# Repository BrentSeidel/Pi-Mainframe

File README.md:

# Pi-Mainframe
Simulated mainframe computer based on a Raspberry Pi

[]
(https://alire.ada.dev/crates/blinkenlights.html)

When I was a young lad, computers had complicated panels filled with
switches and lights.  Sadly, these disappeared as I got older.

This project is an attempt to recreate the feel of old mainframe computers
using a Raspberry Pi 3 and some other assorted parts that I had laying
around.  The actual boxes and panels are 3D printed.

Here is an example system.  Note that it is fairly modular and the
modules can be attached in different ways.

Back of system

## Note
This is still very much a work in progress and things will change.

This project requires 3D printing, making PCBs, soldering, and building
software from source.  It might be a good project for an undergraduate
engineering program.

## Power
I originally used a random micro USB power supply for the Pi 3 that is
running the simulation.  It would complain about low voltage and
occasionally reboot.  I just replaced it with the official Raspberry Pi
power supply and it is not complaining about low voltage.  Time will
tell if it is more stable.

Ultimately, there will be limits to how much power you can get out of
the Raspberry Pi.  There are ways to reduce the power needed.  The first
thing that I would try would be to increase the value of the resistors
for the LEDs.  This would also reduce the brightness so you may wish to
do this as well, if the LEDs are too bright.  A little experimentation
will be needed to determine the proper value.  From a BOM viewpoint,
using the same resistors for both the switches and LEDs would be a win.

## PCBs
Three printed circuit boards have been designed to eliminate some of the
tedious soldering.  Using the PCBs make assembly much easier and the
resulting project much less of a mess of wires.

### IO Board PCB
The I/O board PCB has been created and tested.  The schematics and PCB
layout have been moved to the Circuits reporitory.  Documentation and
assembly instructions for it have been created there.

### Breakout PCB
A breakout PCB has been developed for breaking out the 10 conductor
ribbon cables that are being used for the I2C bus, and other uses.  It
is also in the Circuits repository.

### LED PCB
A PCB has been developed for holding the LEDs.  This required some redesign
to the panels.  However it eliminates the soldering of wires directly to
the LED leads.  The LED PCB can also be fairly easily added to and
removed from panels should you wish to, for example, use LEDs of different
colors.

## Dependencies
This depends on the following repositories:
* https://github.com/BrentSeidel/BBS-Ada.git
* https://github.com/BrentSeidel/BBS-BBB-Ada.git
* https://github.com/BrentSeidel/Ada-Web-Server.git
* https://github.com/BrentSeidel/Things.git
* https://github.com/BrentSeidel/Sim-CPU.git
* https://github.com/BrentSeidel/Circuits.git

If you are actually interested in simulating old computers, you can
download and build simh from github at https://github.com/simh/simh.git
I was able to get the PDP-11 sim to build (I haven't tried others) and
run on a Raspberry Pi.  As far as I know, it has no support for blinking
lights.

You could, of course run simh in parallel with this project giving a
CPU simulation as well as lights and switches.  Unfortunately, they would
be completely independant.  Someday, perhaps this will change.

## Assembly
This project will require quite a bit of 3D printing and soldering.  The
included documentation includes a parts list.  Read the documentation
first, then download the dependencies repositories.  Finally decided
how big of a system you want.
1. Slice the 3D models and start them printing.  This will take a while,
   so start this first and then work on other things while they are printing.
2. Install Raspberian on the Raspberry Pi and install the following packages:
   * avahi - This allows discovery on your local network
   * gnat - The GNU Ada distribution
   * gprbuild - Used for building Ada software
3. Build the software.  If there are errors about missing "obj" directories,
   create the directories.
4. Start soldering the various boards and cables.
5. As panels come off the printer, install LEDs and switches as appropriate
6. As the trays come off the printer, install the boards and connectors.
7. Once everything is printed, put all the pieces together.

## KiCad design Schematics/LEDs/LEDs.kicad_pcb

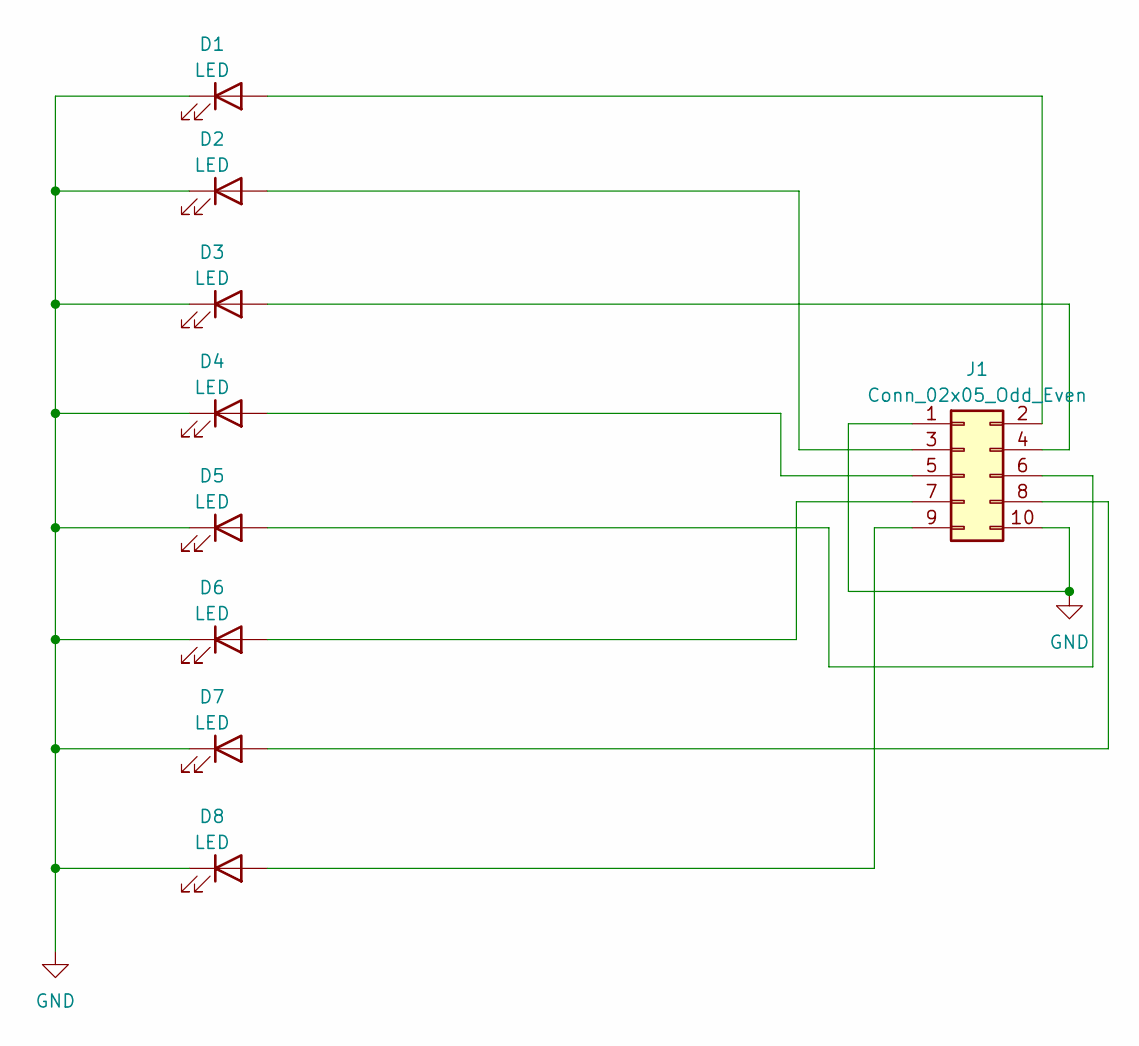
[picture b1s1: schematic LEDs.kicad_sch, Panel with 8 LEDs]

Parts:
D1, D2, D3, D4, D5, D6, D7, D8: LED; LED_D5.0mm_Clear
J1: Conn_02x05_Odd_Even; PinHeader_2x05_P2.54mm_Horizontal

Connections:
GND: D1.1 (K), D2.1 (K), D3.1 (K), D4.1 (K), D5.1 (K), D6.1 (K), D7.1 (K), D8.1 (K), J1.1, J1.10
unnamed: D1.2 (A), J1.2
unnamed: D2.2 (A), J1.3
unnamed: D3.2 (A), J1.4
unnamed: D4.2 (A), J1.5
unnamed: D5.2 (A), J1.6
unnamed: D6.2 (A), J1.7
unnamed: D7.2 (A), J1.8
unnamed: D8.2 (A), J1.9

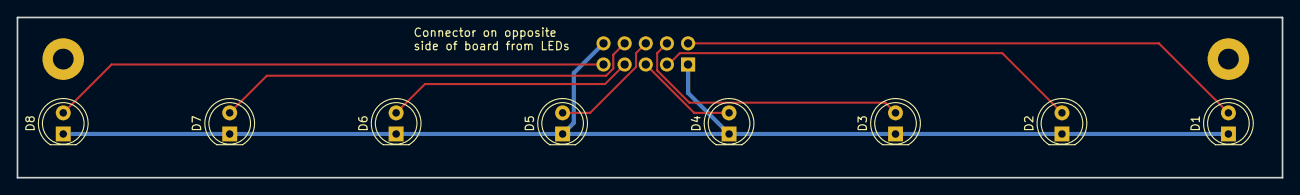
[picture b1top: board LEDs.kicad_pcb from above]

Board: 2 copper layers, 152.0 x 19.2 mm, 11 parts (1 on the bottom side), 9 nets.

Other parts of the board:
REF1, REF2: MountingHole_2.5mm_Pad

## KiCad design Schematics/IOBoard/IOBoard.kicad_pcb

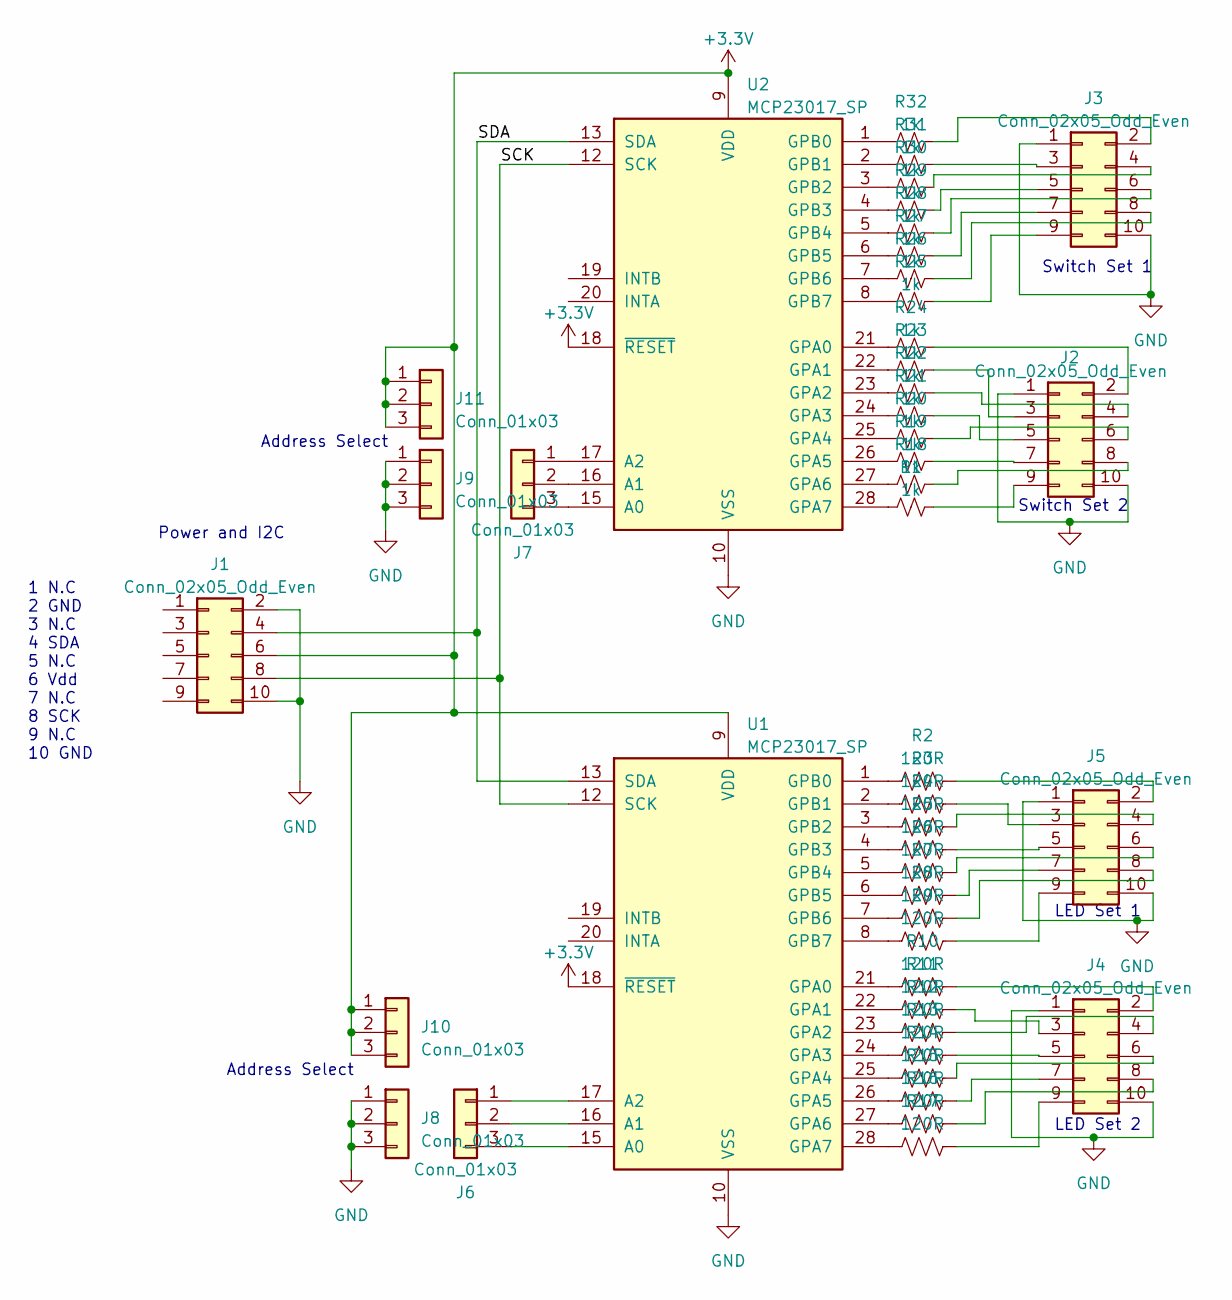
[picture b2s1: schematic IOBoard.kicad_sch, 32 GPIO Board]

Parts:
J1, J2, J3, J4, J5: Conn_02x05_Odd_Even; PinHeader_2x05_P2.54mm_Horizontal
J6, J7, J8, J9, J10, J11: Conn_01x03; PinSocket_1x03_P2.54mm_Vertical
R1, R18, R19, R20, R21, R22, R23, R24, R25, R26, R27, R28, R29, R30, R31, R32: 1k; R_1206_3216Metric_Pad1.30x1.75mm_HandSolder
R2, R3, R4, R5, R6, R7, R8, R9, R10, R11, R12, R13, R14, R15, R16, R17: 120R; R_1206_3216Metric_Pad1.30x1.75mm_HandSolder
U1, U2: MCP23017_SP; DIP-28_W7.62mm

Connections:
+3.3V: J1.6, J10.1, J10.2, J10.3, J11.1, J11.2, J11.3, U1.9 (VDD), U1.18 (~RESET), U2.9 (VDD), U2.18 (~RESET)
/SCK: J1.8, U1.12 (SCK), U2.12 (SCK)
/SDA: J1.4, U1.13 (SDA), U2.13 (SDA)
GND: J1.2, J1.10, J2.1, J2.10, J3.1, J3.10, J4.1, J4.10, J5.1, J5.10, J8.1, J8.2, J8.3, J9.1, J9.2, J9.3, U1.10 (VSS), U2.10 (VSS)
unnamed: J2.2, R24.2
unnamed: J2.3, R23.2
unnamed: J2.4, R22.2
unnamed: J2.5, R21.2
unnamed: J2.6, R20.2
unnamed: J2.7, R19.2
unnamed: J2.8, R18.2
unnamed: J2.9, R1.2
unnamed: J3.2, R32.2
unnamed: J3.3, R31.2
unnamed: J3.4, R30.2
unnamed: J3.5, R29.2
unnamed: J3.6, R28.2
unnamed: J3.7, R27.2
unnamed: J3.8, R26.2
unnamed: J3.9, R25.2
unnamed: J4.2, R10.1
unnamed: J4.3, R11.1
unnamed: J4.4, R12.1
unnamed: J4.5, R13.1
unnamed: J4.6, R14.1
unnamed: J4.7, R15.1
unnamed: J4.8, R16.1
unnamed: J4.9, R17.1
unnamed: J5.2, R2.1
unnamed: J5.3, R3.1
unnamed: J5.4, R4.1
unnamed: J5.5, R5.1
unnamed: J5.6, R6.1
unnamed: J5.7, R7.1
unnamed: J5.8, R8.1
unnamed: J5.9, R9.1
unnamed: J6.1, U1.17 (A2)
unnamed: J6.2, U1.16 (A1)
unnamed: J6.3, U1.15 (A0)
unnamed: J7.1, U2.17 (A2)
unnamed: J7.2, U2.16 (A1)
unnamed: J7.3, U2.15 (A0)
unnamed: R10.2, U1.21 (GPA0)
unnamed: R11.2, U1.22 (GPA1)
unnamed: R12.2, U1.23 (GPA2)
unnamed: R13.2, U1.24 (GPA3)
unnamed: R14.2, U1.25 (GPA4)
unnamed: R15.2, U1.26 (GPA5)
unnamed: R16.2, U1.27 (GPA6)
unnamed: R17.2, U1.28 (GPA7)
unnamed: R2.2, U1.1 (GPB0)
unnamed: R3.2, U1.2 (GPB1)
unnamed: R4.2, U1.3 (GPB2)
unnamed: R5.2, U1.4 (GPB3)
unnamed: R6.2, U1.5 (GPB4)
unnamed: R7.2, U1.6 (GPB5)
unnamed: R8.2, U1.7 (GPB6)
unnamed: R9.2, U1.8 (GPB7)
unnamed: R24.1, U2.21 (GPA0)
unnamed: R23.1, U2.22 (GPA1)
unnamed: R22.1, U2.23 (GPA2)
unnamed: R21.1, U2.24 (GPA3)
unnamed: R20.1, U2.25 (GPA4)
unnamed: R19.1, U2.26 (GPA5)
unnamed: R18.1, U2.27 (GPA6)
unnamed: R1.1, U2.28 (GPA7)
unnamed: R32.1, U2.1 (GPB0)
unnamed: R31.1, U2.2 (GPB1)
unnamed: R30.1, U2.3 (GPB2)
unnamed: R29.1, U2.4 (GPB3)
unnamed: R28.1, U2.5 (GPB4)
unnamed: R27.1, U2.6 (GPB5)
unnamed: R26.1, U2.7 (GPB6)
unnamed: R25.1, U2.8 (GPB7)

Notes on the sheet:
1 N.C 2 GND 3 N.C 4 SDA 5 N.C 6 Vdd 7 N.C 8 SCK 9 N.C 10 GND
Power and I2C
Switch Set 1
Address Select
LED Set 1
LED Set 2
Switch Set 2

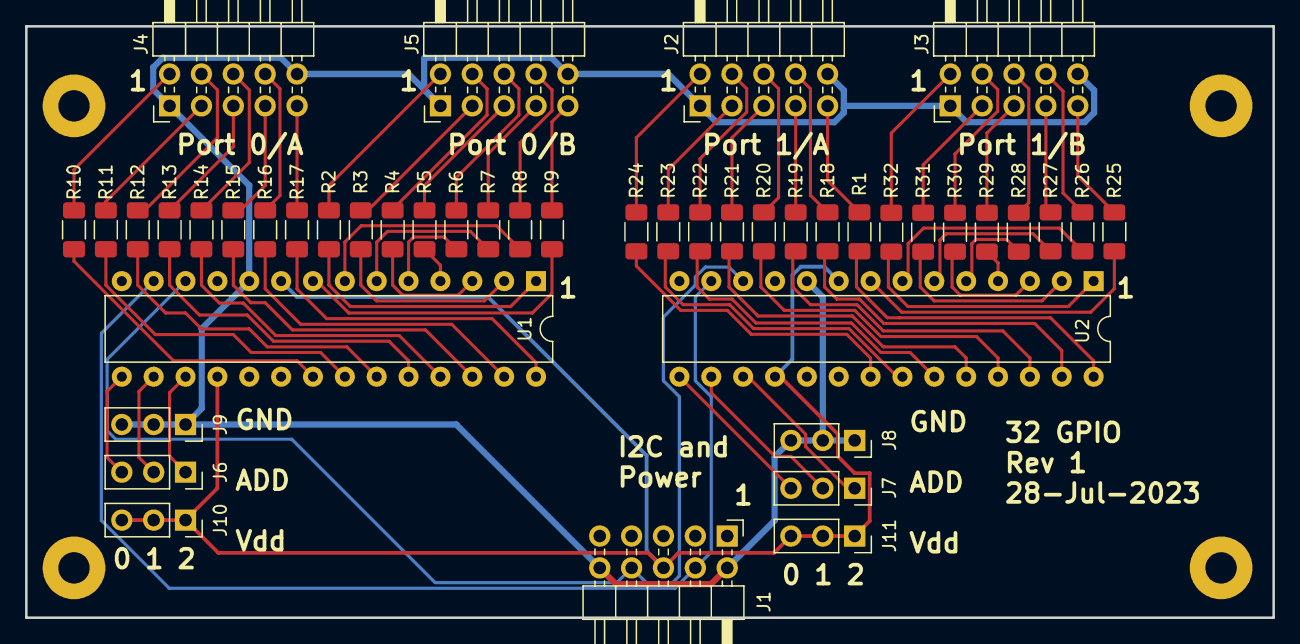
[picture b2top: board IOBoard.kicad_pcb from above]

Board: 2 copper layers, 99.4 x 47.1 mm, 49 parts (0 on the bottom side), 74 nets.

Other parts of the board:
H1, H2, H3, H4: MountingHole_2.5mm_Pad

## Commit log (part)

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2021-09-12 First commit with OpenSCAD files for 3D printed objects.
2021-09-12 Add the initial Ada software.
2021-09-14 Use enumeration with representation clauses for MCP23017 devices so that the addresses are encapsulated.
    Update project file to reference Ada-Web-Server.
2021-09-14 Typo correction - change i2c.SWITCH_MSW to i2c.SWITCH_LSW.
2021-09-15 Add web server - it doesn't do much yet. Change patterns to a task.
2021-09-15 Restructure the patterns code to eliminate a circular dependency.
2021-09-15 Further web server development - add a page to show hardware configuration.
2021-09-16 Add documentation files with outlines.
2021-09-17 Start working on documentation and add documentation to web pages.
2021-09-21 Restructure code a bit and start adding AJAX for interfacing to the simulator via a web page.
2021-09-21 Updates to start to allow remote control of simulator.
2021-09-22 Some doc and hardware updates. Work on interface between i2c and simulator.
2021-09-22 Work on simulator interface some more.
2021-09-23 Add display of panel register values.
2021-09-23 Documentation updates and a minor update to control panel labels.
2021-09-28 Documentation updates and add some assembly pictures.
2021-09-29 Documentation updates with figures to add instructions for wiring LEDs on panels.
2021-10-05 Documentation updates. Add a power panel. S/W updates to start working witn control and mode panels.
2021-10-06 Documentation updates and add a couple of assembly images.
2021-10-07 More documentation updates.
2021-10-08 Documentation updates - add more assembly instructions and photos.
2021-10-08 Update hardware configuration code to support mode/control LEDs.
2021-10-08 Extend test patterns to include mode/control LEDs.
2021-10-08 Minor tweaks to test patterns.
2021-10-08 Minor tweaks to test patterns. Add a construction photo for later inclusion into documentation.
2021-10-10 Update software to be able to test control switches.
2021-10-11 Initial code to let the auto/man switch enable/disable remote control.
2021-10-12 Update documentation to show switch wiring.
    Increase size of rack flanges and work on incorporating control switch
    functions into software.
    Process pictures to reduce their size and the size of the documents.
    Squashed some commits to avoid sending too large files to GitHub.
2021-10-12 Fix bug in allowing deposit to select test pattern.
2021-10-12 Move exception handler to top level to turn out the lights when exiting. Some changes to switch change logic to clear changes at the end of the loop.
2021-10-13 More work on control switch logic and reduction of redundant I2C messages.
2021-10-13 Allow web server to request simulator exit
2021-10-15 Documentation updates and some minor internal changes to simulator. Adjust the spacing of mounting holes for rack adapters.
2021-10-20 Add program to test lights and switches
2021-10-20 Updates to lamp test.
2021-10-21 Add 16 and 32 bit versions of bounce and scan test patterns.
2021-10-21 Update web page javascript to account for new sim patterns.
2021-10-22 Documentation updates.
2021-11-22 Correct typo in documentation.
2022-01-10 Start work on using represenation clauses for boolean values rather than doing the bit twiddling in code.
2022-01-10 More work on using representation clauses.
2022-01-10 More cleanup from represenation clauses.
2022-01-11 More cleanup with represenation clauses.
2022-01-11 Make switch register values read-only outside of sim package.
2022-01-11 Rename package "sim" to "panel" in preparation for separating the panel interface from the simulators.
2022-01-11 More cleanup and refactoring.
2022-01-12 Fix bug related to detecting switch changes.
2022-01-13 Start work on breaking simulators out from panels.
2022-01-13 More work on turning simulator into an object.
2022-01-13 Start removing old simulator code from panels package.
2022-01-14 Updates to simulator interface.
2022-01-14 Fill in code for deposit to show the value deposited.
2022-01-18 Change way that Address/Data switch is handled. Start preparing simulator for breakout into a separate repository.
2022-01-18 Move simulators into BBS package hierarchy. Add web page to show simulator information and register values.
2022-01-18 Fix stub return register value routine to actually return register value instead of 0.
2022-01-19 Updates to improve the display of register values.
2022-01-19 Move definitions for mode/control types to sim package.
2022-01-19 Remove simulator dependence on Panel package.
2022-01-19 Add missing code to communicate panel data with the simulator.
2022-01-20 Some internal code cleanup and make the simulator control web page ensure that the correct simulator is running.
2022-01-21 Change package name "Sim" to "Sim_CPU" as I may wish to support other kinds of simulations. Other minor code cleanup.
2022-01-21 Moved simulator files into Sim-CPU repository and made updates to point to that project. Also fixed a couple typos in comments in i2c.ads
2022-01-21 Update README to point to Sim-CPU repository as a dependency.
2023-05-28 Start working on schematics and board layout for I/O board. If nothing else, the schematics will provide some documentation about how things should be wired up. Note that this may not be consistent w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
2023-06-13 Update schematic and PCB to use resistor symbols instead of jumpers.
2023-06-19 Update PCB to use SMD resistors and rectangular connectors. This lets the PCB shrink some more and it may be easier to crimp rectangular connectors onto ribbon cable than to solder a bunch of D-9 con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
2023-07-09 Update schematic to add resisters on inputs as well. Submitted PCB for production. Once PCBs are received, assembled, tested, and working, I'll update documentation.
2023-07-24 Fix schematic error and re-layout board. Start a tray to hold board.
2023-07-26 More updates to I/O board PCB layout.
2023-07-28 Updates to PCB layout to add silkscreen blocks for notes.
2023-08-09 Updates to panels. Delete unused stuff and modify labels.
2023-08-11 Remove I/O Board design now that it has been moved to the Circuits repository.
2023-08-14 Update README.md
    Correct typo in link to Circuits repository.
2023-08-15 Work on CPU tray to incorporate the breakout board from the circuits repository. Work on I/O tray to use the new GPIO board from the circuits repository.
2023-08-15 Use Ribbon-10 breakout board model instead of local breakout model.
2023-08-17 Add PCB for LEDs and update panels to use the PCB.
2023-08-18 Update the README to give current status.
2023-08-30 Adjust the IO tray so that the IO board lines up with the connector from the processor board. This makes the ribbon cable easier to run.
2023-08-31 Move documentation to prepare for documentation for new hardware. Also minor change to code to be consistent with changes to Sim-CPU.
2023-09-01 Start working on assmebly instructions for new hardware with custom PCBs.
2023-09-01 Update panels for LED PCBs.
2023-09-04 Add documentation for assembling the LED PCBs.
2023-09-04 Updates to lamp test program to add a sequence pattern.
2023-09-04 Updates to documentation to include assembly of panels.
2023-09-05 More documentation updates. The new documentation should be nearly complete.
2023-09-05 Minor updates to documentation primarily to fix table references.
2023-09-06 Remove some old hardware details from new hardware documentation.
2023-09-06 Minor updates to start working with multiple simulations.
2023-09-13 Add photos of a completed system.
2023-09-13 Update README.md
    Fix markdown code for image in README.
2023-09-19 Update to README about power supply and consumption/
2023-09-20 Minor changes to support hardware debugging and cleanup.
2023-11-06 Correct spelling of "engergisze" on power panel, per Issue #1.
2023-11-06 Update README.md
    Delete extra backslash from LED PCB heading.
2023-11-14 Updates to run with 8080 simulator.
2023-11-15 Updates to improve status LED display.
2024-01-22 Updates to be consistent with changes in other projets (mainly uint definitions moving from BBS.embed to BBS.
2024-03-20 Updates to add 68000 simulator and make work with other package changes.
2024-03-20 Call initialization for 68000 CPU. Add sample OS and Task files for 68000 CPU. Move project to use alire.
2024-05-02 Update code to allow simulator selection on program entry.
2024-05-07 Add missing attach of clock to 68000 init. Add mux device to 68000 init.
2024-05-07 Add line to set the clock's base rate. Add updated OS68k.
2024-05-07 Add updated tasks for OS68k.
2024-08-07 Updates to account for changes in other projects.
2024-08-09 Update *.gpr files to account for changes to BBS-BBB-Ada (bbs.embed.* packages).
2024-08-14 Rename projects and executables in preparation for alr publish.
2024-08-14 Prepare for alr publish.
2024-08-14 Update version number.
2024-08-20 Add alire badge to README.
2024-09-11 Update to work with MCP23017 changes. Update to new alire version number. Fix *_noalire.gpr project name.
2024-09-20 Use I2C addresses from BBS.embed.i2c.devices.
2025-03-09 Update to work with the latest (v0.3.2) version of bbs_simcpu.
2025-03-10 Change dependency in bbs_embed_linux to 0.2.0
2025-03-10 Fix alr dependencies.
2025-03-10 Update alr dependency on bbs-embed-linux to v0.2.0.
2025-09-16 Updates to build with changes to Sim_CPU.
2025-10-20 Update to work with Sim-CPU bus updates.
2025-11-26 Update to prepare for alr publish.
